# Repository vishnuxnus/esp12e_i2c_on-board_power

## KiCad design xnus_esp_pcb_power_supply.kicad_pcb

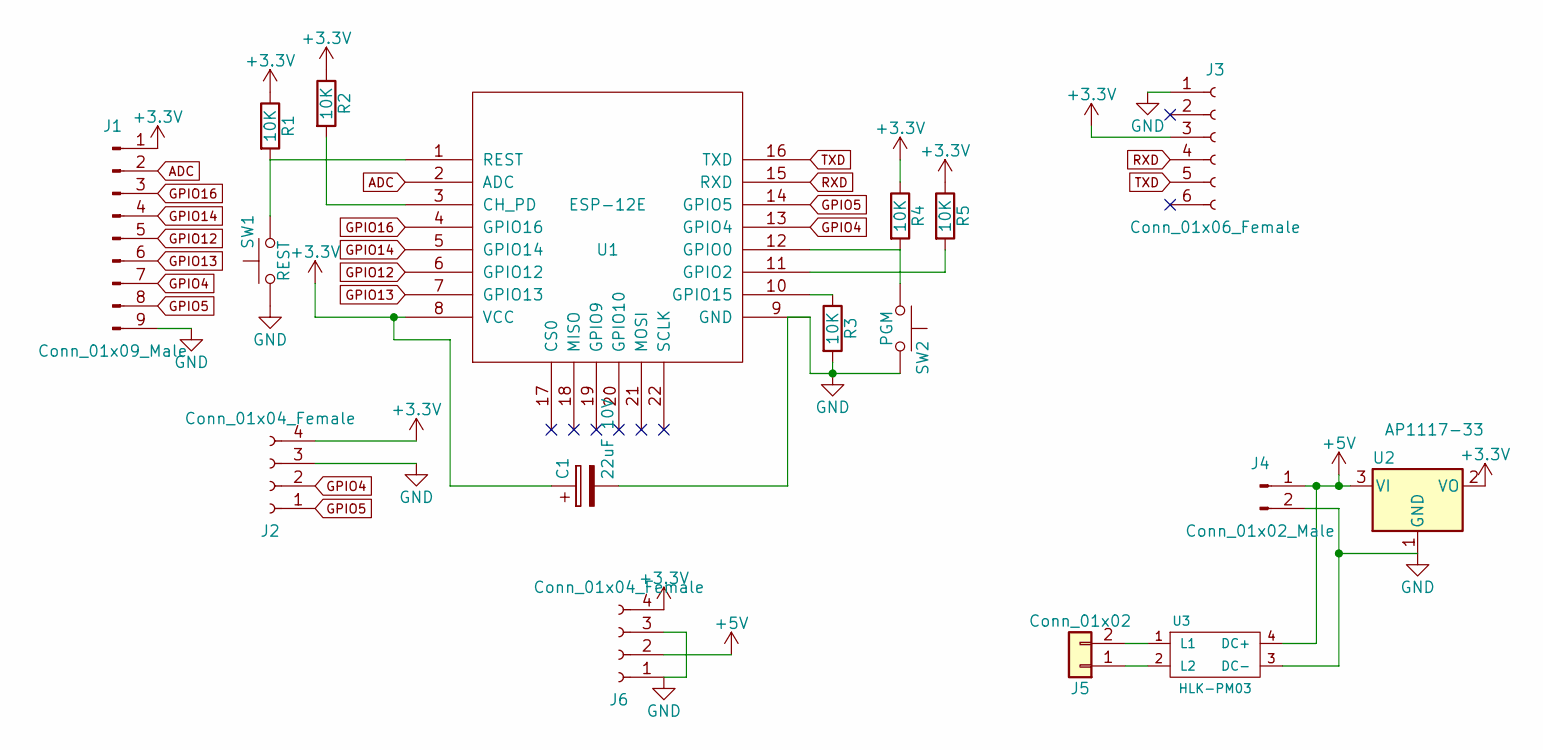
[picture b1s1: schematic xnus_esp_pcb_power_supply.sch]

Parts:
C1: 22uF 10V; CP_Radial_D5.0mm_P2.50mm
J1: Conn_01x09_Male; Pin_Header_Straight_1x09_Pitch2.54mm
J2: Conn_01x04_Female; Pin_Header_Angled_1x04_Pitch2.54mm
J3: Conn_01x06_Female; Socket_Strip_Straight_1x06_Pitch2.54mm
J4: Conn_01x02_Male; JST_EH_B02B-EH-A_02x2.50mm_Straight
J5: Conn_01x02; TerminalBlock_bornier-2_P5.08mm
J6: Conn_01x04_Female; Pin_Header_Straight_1x04_Pitch2.54mm
R1, R2, R3, R4, R5: 10K; R_Axial_DIN0204_L3.6mm_D1.6mm_P5.08mm_Horizontal
SW1: REST; SW_PUSH_6mm
SW2: PGM; SW_PUSH_6mm
U1: ESP-12E
U2: AP1117-33; SOT-223-3_TabPin2
U3: HLK-PM03; HLK-PM01

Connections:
+3V3: C1.1, J1.1, J2.4, J3.3, J6.4, R1.1, R2.1, R4.1, R5.1, U1.8 (VCC), U2.2 (VO)
+5V: J4.1, J6.2, U2.3 (VI), U3.4 (DC+)
ADC: J1.2, U1.2 (ADC)
GND: C1.2, J1.9, J2.3, J3.1, J4.2, J6.1, J6.3, R3.2, SW1.1, SW2.2, U1.9 (GND), U2.1 (GND), U3.3 (DC-)
GPIO4: J1.7, J2.2, U1.13 (GPIO4)
GPIO5: J1.8, J2.1, U1.14 (GPIO5)
GPIO12: J1.5, U1.6 (GPIO12)
GPIO13: J1.6, U1.7 (GPIO13)
GPIO14: J1.4, U1.5 (GPIO14)
GPIO16: J1.3, U1.4 (GPIO16)
unnamed: J5.1, U3.2 (L2)
unnamed: J5.2, U3.1 (L1)
unnamed: R1.2, SW1.2, U1.1 (REST)
unnamed: R2.2, U1.3 (CH_PD)
unnamed: R3.1, U1.10 (GPIO15)
unnamed: R4.2, SW2.1, U1.12 (GPIO0)
unnamed: R5.2, U1.11 (GPIO2)
RXD: J3.4, U1.15 (RXD)
TXD: J3.5, U1.16 (TXD)

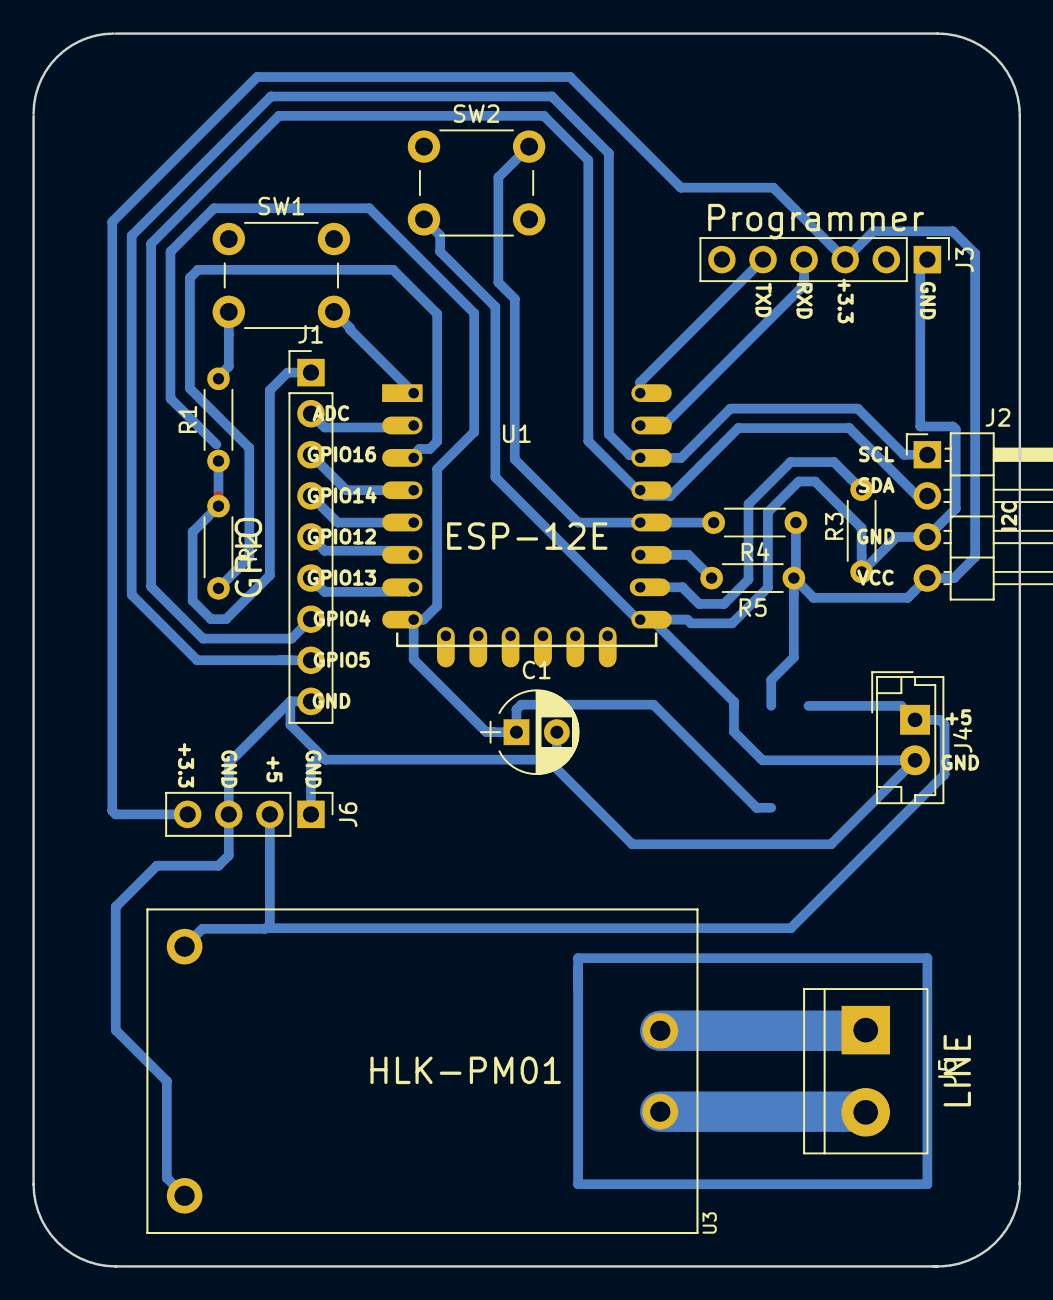
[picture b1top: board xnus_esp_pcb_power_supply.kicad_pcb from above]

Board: 2 copper layers, 61.0 x 76.2 mm, 17 parts (1 on the bottom side), 19 nets.

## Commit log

2018-02-15 Inital Commit
